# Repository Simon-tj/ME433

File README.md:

# ME433
Repo for ME: 433 - Adv. Mech. - SQ21

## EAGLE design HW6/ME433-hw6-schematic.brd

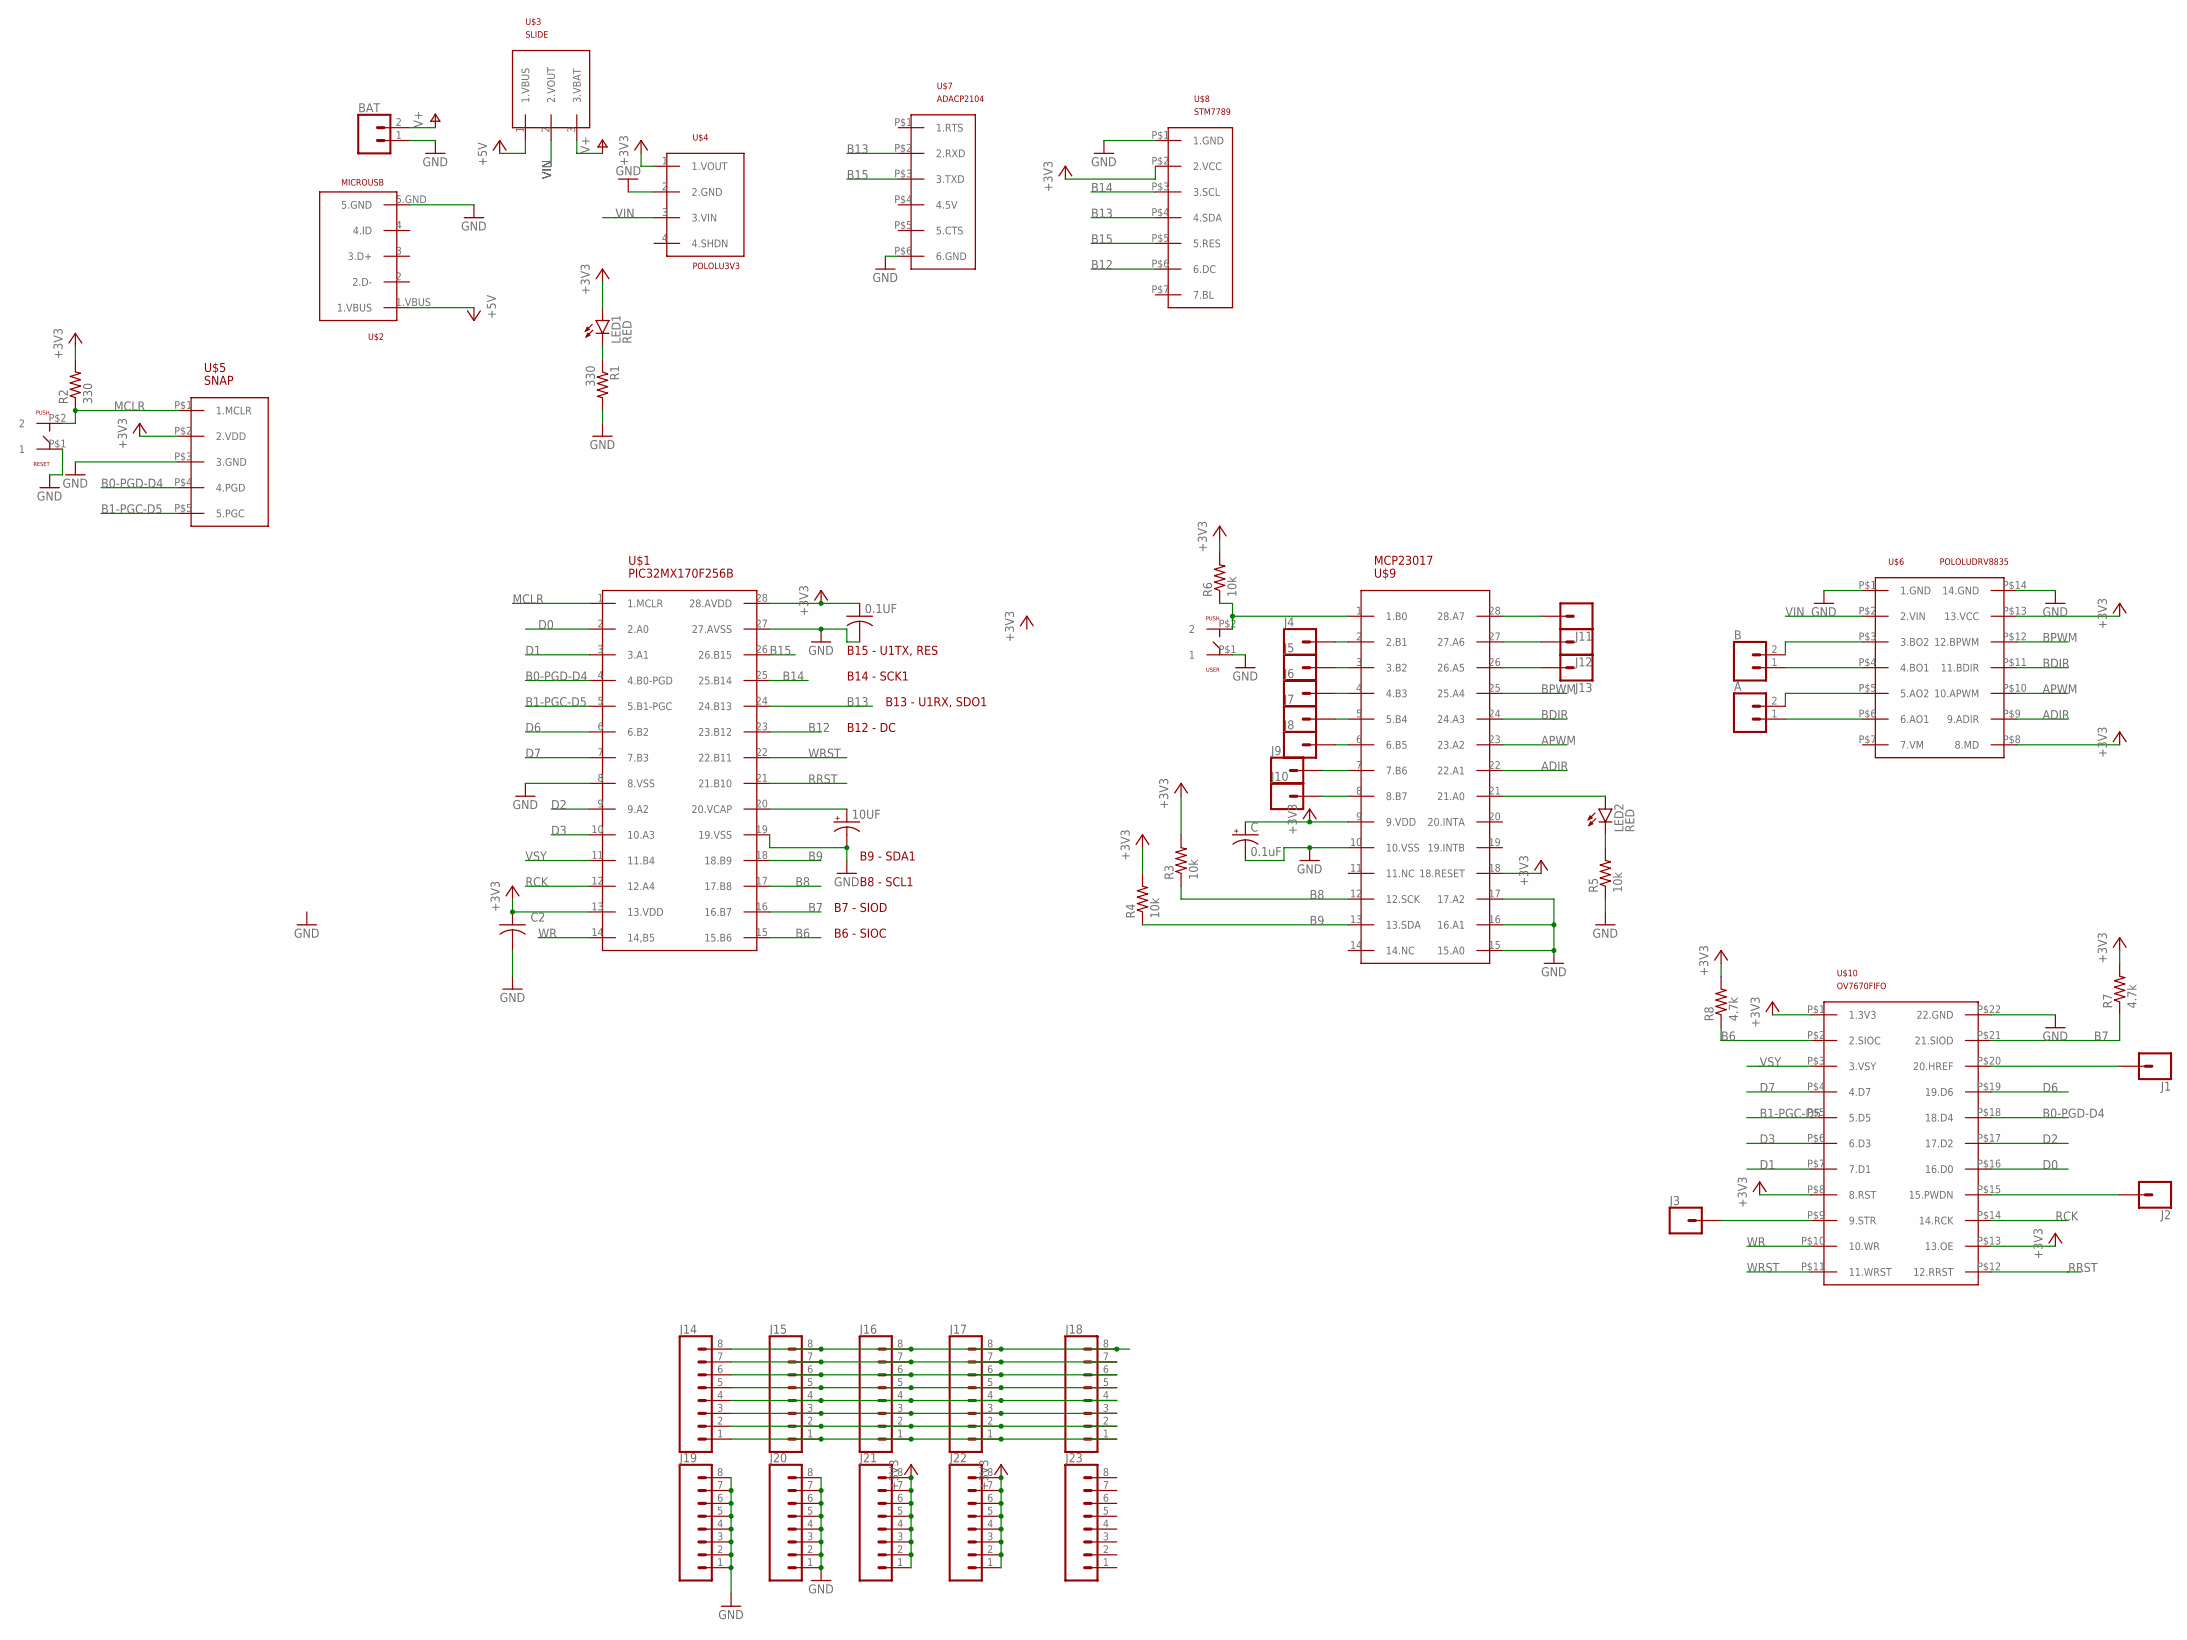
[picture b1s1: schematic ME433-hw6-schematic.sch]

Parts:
0.1UF: C-US025-030X050; C025-030X050
10UF: CPOL-USB45181B; B45181B
A: CONN_02; 1X02
B: CONN_02; 1X02
BAT: CONN_02; 1X02
C: 0.1uF; B45181B
C2: C-US025-030X050; C025-030X050
J1, J2, J3, J4, J5, J6, J7, J8, J9, J10, J11, J12, J13: CONN_01; 1X01
J14, J15, J16, J17, J18, J19, J20, J21, J22, J23: CONN_08"; 1X08
LED1, LED2: RED; LED3MM
R1, R2: 330; 0207/10
R3, R4, R5, R6: 10k; 0207/10
R7, R8: 4.7k; 0207/10
RESET: PUSH
U$1: PIC32MX170F256B; DIL28-3
U$2: MICROUSB
U$3: SLIDE
U$4: POLOLU3V3
U$5: SNAP
U$6: POLOLUDRV8835
U$7: ADACP2104
U$8: STM7789
U$9: MCP23017
U$10: OV7670FIFO
USER: PUSH

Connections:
+3V3: 0.1UF.1, C.+, C2.1, J21.1, J21.2, J21.3, J21.4, J21.5, J21.6, J21.7, J21.8, J22.1, J22.2, J22.3, J22.4, J22.5, J22.6, J22.7, J22.8, LED1.A, R2.2, R3.2, R4.2, R6.2, R7.2, R8.2, U$1.13 (13.VDD), U$1.28 (28.AVDD), U$4.1 (1.VOUT), U$5.P$2 (2.VDD), U$6.P$8 (8.MD), U$6.P$13 (13.VCC), U$8.P$2 (2.VCC), U$9.9 (9.VDD), U$9.18 (18.RESET), U$10.P$1 (1.3V3), U$10.P$8 (8.RST), U$10.P$13 (13.OE)
+5V: U$2.1.VBUS, U$3.1 (1.VBUS)
ADIR: U$6.P$9 (9.ADIR), U$9.22 (22.A1)
APWM: U$6.P$10 (10.APWM), U$9.23 (23.A2)
B0-PGD-D4: U$1.4 (4.B0-PGD), U$5.P$4 (4.PGD), U$10.P$18 (18.D4)
B1-PGC-D5: U$1.5 (5.B1-PGC), U$5.P$5 (5.PGC), U$10.P$5 (5.D5)
B6: R8.1, U$1.15 (15.B6), U$10.P$2 (2.SIOC)
B7: R7.1, U$1.16 (16.B7), U$10.P$21 (21.SIOD)
B8: R3.1, U$1.17 (17.B8), U$9.12 (12.SCK)
B9: R4.1, U$1.18 (18.B9), U$9.13 (13.SDA)
B12: U$1.23 (23.B12), U$8.P$6 (6.DC)
B13: U$1.24 (24.B13), U$7.P$2 (2.RXD), U$8.P$4 (4.SDA)
B14: U$1.25 (25.B14), U$8.P$3 (3.SCL)
B15: U$1.26 (26.B15), U$7.P$3 (3.TXD), U$8.P$5 (5.RES)
BDIR: U$6.P$11 (11.BDIR), U$9.24 (24.A3)
BPWM: U$6.P$12 (12.BPWM), U$9.25 (25.A4)
D0: U$1.2 (2.A0), U$10.P$16 (16.D0)
D1: U$1.3 (3.A1), U$10.P$7 (7.D1)
D2: U$1.9 (9.A2), U$10.P$17 (17.D2)
D3: U$1.10 (10.A3), U$10.P$6 (6.D3)
D6: U$1.6 (6.B2), U$10.P$19 (19.D6)
D7: U$1.7 (7.B3), U$10.P$4 (4.D7)
GND: 0.1UF.2, 10UF.-, BAT.1, C.-, C2.2, J19.1, J19.2, J19.3, J19.4, J19.5, J19.6, J19.7, J19.8, J20.1, J20.2, J20.3, J20.4, J20.5, J20.6, J20.7, J20.8, R1.2, R5.1, RESET.P$1 (1), U$1.8 (8.VSS), U$1.19 (19.VSS), U$1.27 (27.AVSS), U$2.5.GND, U$4.2 (2.GND), U$5.P$3 (3.GND), U$6.P$1 (1.GND), U$6.P$14 (14.GND), U$7.P$6 (6.GND), U$8.P$1 (1.GND), U$9.10 (10.VSS), U$9.15 (15.A0), U$9.16 (16.A1), U$9.17 (17.A2), U$10.P$22 (22.GND), USER.P$1 (1)
MCLR: R2.1, RESET.P$2 (2), U$1.1 (1.MCLR), U$5.P$1 (1.MCLR)
unnamed: LED1.K (C), R1.1
unnamed: LED2.K (C), R5.2
unnamed: B.2, U$6.P$3 (3.BO2)
unnamed: 10UF.+, U$1.20 (20.VCAP)
unnamed: LED2.A, U$9.21 (21.A0)
unnamed: R6.1, U$9.1 (1.B0), USER.P$2 (2)
unnamed: B.1, U$6.P$4 (4.BO1)
unnamed: A.2, U$6.P$5 (5.AO2)
unnamed: A.1, U$6.P$6 (6.AO1)
unnamed: J3.1, U$10.P$9 (9.STR)
unnamed: J2.1, U$10.P$15 (15.PWDN)
unnamed: J1.1, U$10.P$20 (20.HREF)
unnamed: J4.1, U$9.2 (2.B1)
unnamed: J5.1, U$9.3 (3.B2)
unnamed: J6.1, U$9.4 (4.B3)
unnamed: J7.1, U$9.5 (5.B4)
unnamed: J8.1, U$9.6 (6.B5)
unnamed: J9.1, U$9.7 (7.B6)
unnamed: J10.1, U$9.8 (8.B7)
unnamed: J11.1, U$9.28 (28.A7)
unnamed: J12.1, U$9.27 (27.A6)
unnamed: J13.1, U$9.26 (26.A5)
unnamed: J14.8, J15.8, J16.8, J17.8, J18.8
unnamed: J14.7, J15.7, J16.7, J17.7, J18.7
unnamed: J14.6, J15.6, J16.6, J17.6, J18.6
unnamed: J14.5, J15.5, J16.5, J17.5, J18.5
unnamed: J14.4, J15.4, J16.4, J17.4, J18.4
unnamed: J14.3, J15.3, J16.3, J17.3, J18.3
unnamed: J14.2, J15.2, J16.2, J17.2, J18.2
unnamed: J14.1, J15.1, J16.1, J17.1, J18.1
RCK: U$1.12 (12.A4), U$10.P$14 (14.RCK)
RRST: U$1.21 (21.B10), U$10.P$12 (12.RRST)
V+: BAT.2, U$3.3 (3.VBAT)
VIN: U$3.2 (2.VOUT), U$4.3 (3.VIN), U$6.P$2 (2.VIN)
VSY: U$1.11 (11.B4), U$10.P$3 (3.VSY)
WR: U$1.14 (14,B5), U$10.P$10 (10.WR)
WRST: U$1.22 (22.B11), U$10.P$11 (11.WRST)

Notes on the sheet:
B15 - U1TX, RES
B13 - U1RX, SDO1
B14 - SCK1
B12 - DC
B9 - SDA1
B8 - SCL1
B7 - SIOD
B6 - SIOC

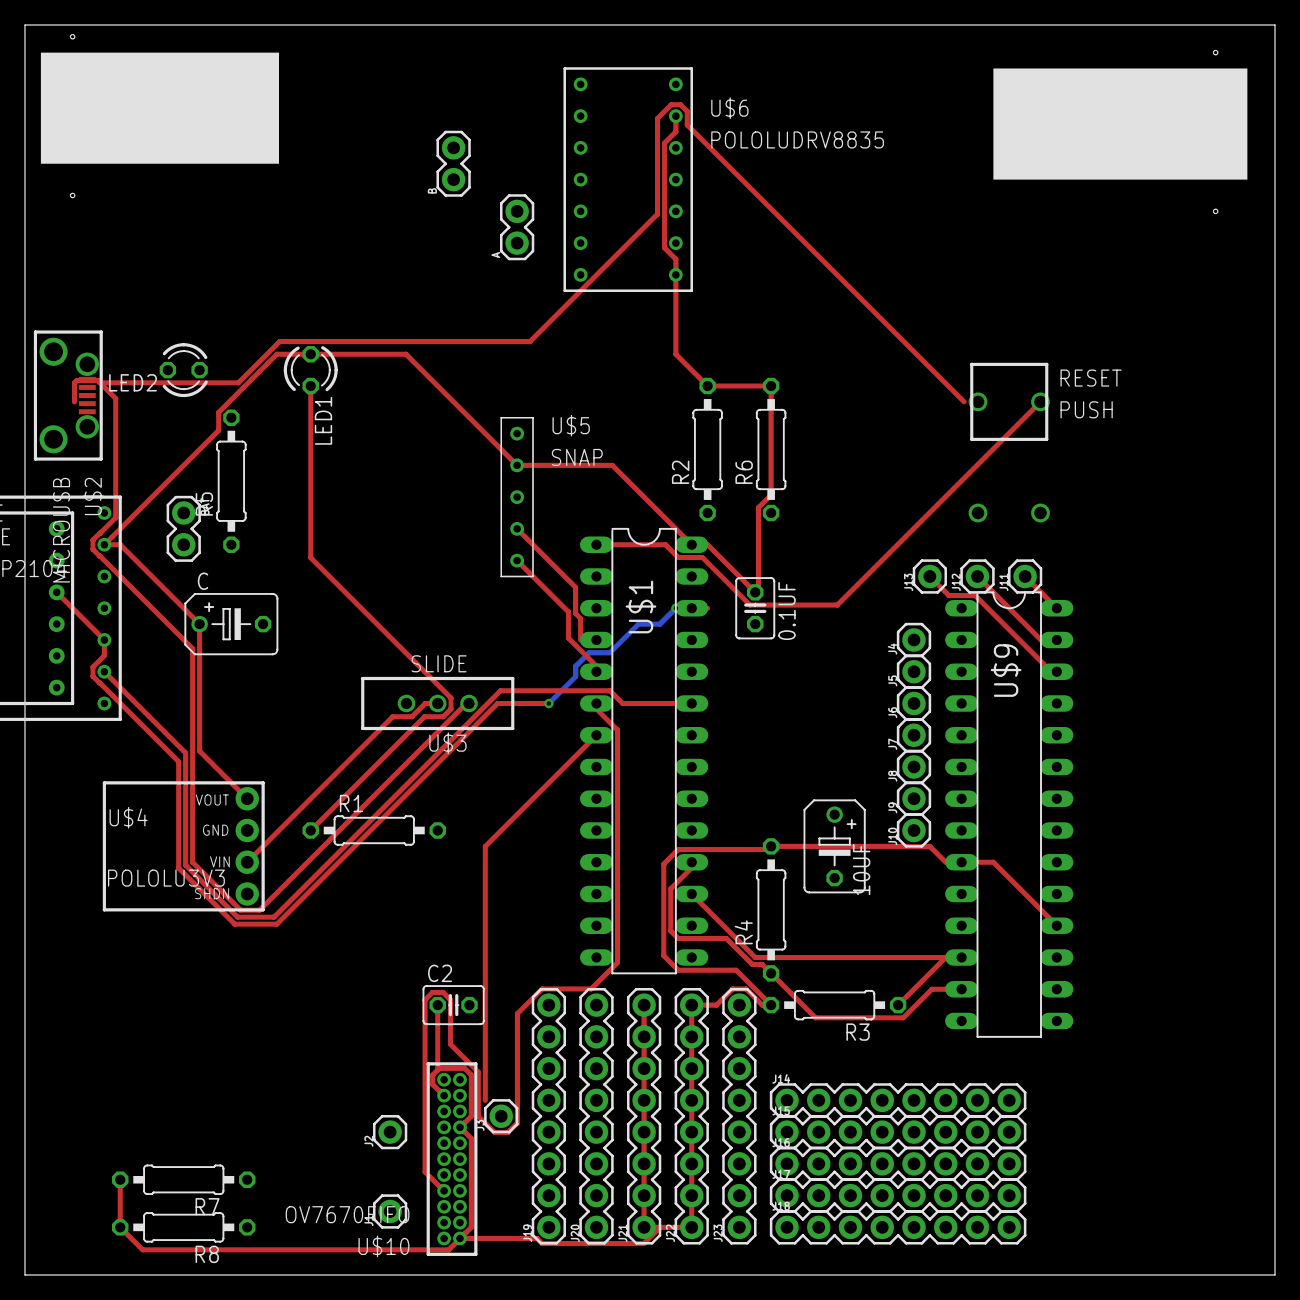
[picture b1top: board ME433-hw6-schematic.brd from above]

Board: 2 copper layers, 100.0 x 100.0 mm, 52 parts (1 on the bottom side), 61 nets.

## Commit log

2021-04-02 Added sig files from HW2-DSP
2021-04-02 Added .py files and completed #1
2021-04-02 Tested plot functions
2021-04-02 Found Samp Rate
2021-04-02 Item 4 - FFT subplots
2021-04-04 Up through Q5
2021-04-04 Through Q6
2021-04-05 Through Q7
2021-04-05 Full graphs
    Was unsure if we should include the csv filtered data or the fft of the filtered data so now included both
2021-04-16 stuff i forgot to commit
2021-04-16 videos for hw4
2021-04-23 hw7 start
2021-05-12 hw10
2021-05-15 hw9 start
2021-05-15 hw9 end
2021-05-16 hw9 vid
2021-06-08 HW10,11, assorted things i forgot
    HW10,11 and assorted other stuff
2021-06-10 hw16
2021-06-10 hw11 vid
